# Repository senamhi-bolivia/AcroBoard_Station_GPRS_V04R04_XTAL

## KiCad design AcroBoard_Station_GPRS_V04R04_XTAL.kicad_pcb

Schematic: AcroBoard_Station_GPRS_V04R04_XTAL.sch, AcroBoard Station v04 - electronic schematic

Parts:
C1, C2, C4, C7, C10, C11, C12, C14, C22, C25, C34, C77, C78, C79, C80, C81, C82: 100nF; C_0603
C3, C16, C17: 1uF; C_0805
C5, C6, C8, C9, C20, C23, C24, C28, C35, C36, C39, C43, C44, C47, C48, C59, C62: 100nF; C_0402_NoSilk
C13: 68uF; CP_Tantalum_Case-D_EIA-7343-31_Reflow
C15, C19, C21: 22pF; C_0402_NoSilk
C18: 68uF; CP_Elec_5x5.8
C26: 470uF; CP_Radial_D10.0mm_P5.00mm
C27: 22uF; C_0805
C29, C30: 1nF; C_0402
C31, C37, C49, C51: 7pF; C_0402_NoSilk
C32, C38, C40: 33pF; C_0402_NoSilk
C33, C45, C46, C52, C53, C63: 4.7uF; C_0805
C41, C42: 22uF; C_1210
C50: 10uF; C_0805
C54, C55, C65, C66: 22uF; C_1206
C56: 330uF; CP_Elec_10x10
C57, C64, C69: 6.8nF; C_0603
C58, C72: 10uF; C_1210
C60, C61, C70, C71, C74, C75: 0.1uF; C_0805
C67: 4.7uF; CP_Elec_4x5.8
C68: 1uF; C_1206
C73: 100uF; CP_Elec_6.3x7.7
C76: 10uF; C_1206
Cv1, Cv2, Cv3: 0.1uF; C_0805
Cvs1, Cvs2, Cvs3: 1uF; C_0805
D1: Blue; LED_0603
D2, D3, D19: Green; LED_0603
D4, D9, D11, D14: SMBJ26CA; D_SMB
D5, D6, D12, D15: 1N4148W-V; D_SOD-123
D7: BZX84C10; SOT-23
D8, D18: STPS2L40U; D_SMB
D10, D13, D16: BAT54JFILM; D_SOD-323
D17: STPS3L40SY; D_SMC
D20: Red; LED_0603
FP1: {55.0,-148.0}; Fiducial_1mm_Dia_2.54mm_Outer_CopperTop
FP2: {55.0,-30.0}; Fiducial_1mm_Dia_2.54mm_Outer_CopperTop
FP3: {125.0,-148.0}; Fiducial_1mm_Dia_2.54mm_Outer_CopperTop
FP4: {125.0,-30.0}; Fiducial_1mm_Dia_2.54mm_Outer_CopperTop
FP5: {84.6,-79.9}; Fiducial_1mm_Dia_2.54mm_Outer_CopperTop
FP6: {90.0,-115.0}; Fiducial_1mm_Dia_2.54mm_Outer_CopperTop
FP7: {116.0,-89.0}; Fiducial_1mm_Dia_2.54mm_Outer_CopperTop
J1: Conn_Coaxial; SMA_THT_Jack_Straight
J2: Conn_01x08; Molex_KK-6410-08_08x2.54mm_Straight
J3: Conn_01x05; Molex_KK-6410-05_05x2.54mm_Straight
J4, J5: CONN_01X10; Molex_KK-6410-10_10x2.54mm_Straight
J6: CONN_01X08; Molex_KK-6410-08_08x2.54mm_Straight
J7: CONN_01X05; Molex_KK-6410-05_05x2.54mm_Straight
L1, L2, L3: FERRITE-BEAD-220ohm; L_0805
L4: INDUCTOR-3.1uH; SER80xx
L5: 10uH; 7447779122
LG1: ACRONET; ACRONET_logo_090
LG2: OSHW; OSHW-Logo_7.5x8mm_SilkScreen
MH1, MH2, MH3, MH4: MH; MountingHole_320_500-NPTH
P1: CONN_02X06; Socket_Strip_Straight_2x06_Pitch2.54mm_SMD
P2: CONN_14X2; Socket_Strip_Straight_2x14_Pitch2.00mm
P3: 10k B=3.380; Measurement_Point_Round-TH_Small
P4: CONN_5X2; Socket_Strip_Straight_2x05_Pitch2.00mm
P5: CONN_5; BM05B-SRSS-TB
P6: CONN_3; Molex_KK-6410-03_03x2.54mm_Straight
Q4: Si2319CDS; SOT-23
Q5, Q9, Q10: BSS138; SOT-23
Q6, Q7, Q8: IRF9362; SOIC-8_3.9x4.9mm_Pitch1.27mm
R1, R2, R65, R66: 4k7; R_0603
R3, R4, R5, R56, R62, R63, R64, R67: 330R; R_0603
R6, R7, R8: 51R; R_0402
R9, R22, R45, R55, R68: 100K; R_0603
R10: 90k; R_0603
R11, R18, R19, R29, R54: 10K; R_0603
R12: 24K; R_0603
R13, R17, R71, R72, R73, R75, R76, R78: 1K; R_0603
R14: 180K; R_0603
R15: 698K; R_0603
R16, R51: 174K; R_0603
R20, R36, R39, R40, R46, R47: 1M; R_0603
R21, R44: 215K; R_0603
R23, R30: 1M02; R_0805
R24, R69: 48K7; R_0805
R25, R32: 76K8; R_0805
R26: 698K; R_0805
R27: 27K; R_0805
R28: 49K9; R_0805
R31: 36K5; R_0805
R33: 0R; R_0805
R34, R35, R49, R50, R53, R79, R80, R81, R82: 309K; R_0603
R37: 73.2K; R_0603
R38, R41, R48: 2k21; R_0603
R42, R43: 1k3; R_0805
R52: 4K7; R_0603
R57: 0R05; R_1206
R58, R61: 5K1; R_0603
R59, R60: 2k0; R_0805
R70, R74, R77: 5K6; R_0603
SW1: DTSM-32S-B
T1, T2, T3, T4, T5, T6, T7, T8, T9, T10: PDTC143XU; SOT-323_SC-70
U1, U2, U3: AT24CM01-SSHD-B; SOIC-8_3.9x4.9mm_Pitch1.27mm
U4: MB85RC1MTPNF-G-JNERE1; SOIC-8_3.9x4.9mm_Pitch1.27mm
U5, U6: SP336EEY-L; TSSOP-28_4.4x9.7mm_Pitch0.65mm
U7: 78723-1001
U8: ESDA6V1-5W6; SOT363_ESDA6V1-5W6
U9: NCP3170; SOIC-8_3.9x4.9mm_Pitch1.27mm
U10: TPS737; SOT-223-6
U11: ATXMEGA256A3U; TQFP-64_14x14mm_Pitch0.8mm
U13: SIM800C; SIMCom_SIM800C
U14: LTC4417IGN; SSOP-24_3.9x8.7mm_Pitch0.635mm
U15, U16, U21, U22: FPF2701MX; SOP-8_FPF2701MX
U17: LT3652EMSE; MSOP12_LT3652EMSE_HandSoldering
U18, U19: ACPL-M21L; SO-5_ACPL-M21L
U20: MIC1555; SOT-23-5
U23: PCA9517ADP; TSSOP-8_3x3mm_Pitch0.65mm
U24: MPL3115A2; LGA-8_3x5mm_Pitch1.25mm
U25: PCAL9554B; TSSOP-16_4.4x5mm_Pitch0.65mm
U26: PCAL9535APW; TSSOP-24_4.4x7.8mm_Pitch0.65mm
Y1: Crystal; Crystal_SMD_MicroCrystal_CC7V-T1A-2pin_3.2x1.5mm

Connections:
/ALT_CHARGE: J3.2, Q10.3 (D), R58.2
/BC_NC_FET: D7.1 (A), Q4.1 (G), R19.1, R22.2
/BC_NTC: P3.1, U17.8 (NTC)
/BC_Timer: C53.2, U17.6 (TIMER)
/BC_Vin: C56.1, C58.1, C59.1, D7.3 (K), D8.1 (K), D19.2 (A), D20.2 (A), J3.5, Q4.2 (S), R22.1, R36.2, R40.2, U17.1 (Vin)
/CLED_CMD: Q5.3 (D), Q10.1 (G), R37.1
/CMD_PSW1: R79.1, U16.4 (ON), U26.16 (P1_3)
/CMD_PSW2: R80.1, U15.4 (ON), U26.15 (P1_2)
/CMD_PSW3: R82.1, U22.4 (ON), U26.14 (P1_1)
/CMD_PSW4: R81.1, U21.4 (ON), U26.13 (P1_0)
/I2C_OUT_SCL: P4.3, U23.2 (SCLA)
/I2C_OUT_SDA: P4.1, U23.3 (SDAA)
/I2C_SIG: P4.7, T3.3 (C)
/I2C_VIN: C79.2, P4.5, U23.1 (VCCA)
/MCU_Status_LED: T1.1 (B), U11.26 (PD0)
/NETLIGHT: T9.1 (B), U13.41 (NETLIGHT)
/NValid1: U14.10 (~VALID1), U26.6 (P0_2)
/NValid2: U14.11 (~VALID2), U26.5 (P0_1)
/NValid3: U14.12 (~VALID3), U26.4 (P0_0)
/N_SHDN: R18.1, U14.2 (~SHDN)
/OC1: J7.2, R62.2
/OC2: J7.3, R63.2
/OC3: J7.4, R64.2
/OC4: J7.5, R67.2
/PA0: C34.1, P2.1, U11.62 (PA0)
/PA1: R10.2, R11.1, U11.63 (PA1)
/PA2: P2.3, U11.64 (PA2)
/PA3: P2.5, U11.1 (PA3)
/PA4: P2.7, U11.2 (PA4)
/PA5: P2.9, U11.3 (PA5)
/PA6: P2.11, U11.4 (PA6)
/PA7: P2.13, U11.5 (PA7)
/PB0: C35.1, P2.15, U11.6 (PB0)
/PB1: P2.17, U11.7 (PB1)
/PB2: P2.19, U11.8 (PB2)
/PB3: P2.21, U11.9 (PB3)
/PB4: P2.23, U11.10 (PB4)
/PB5: P2.25, U11.11 (PB5)
/PB6: P2.27, U11.12 (PB6)
/PB7: U11.13 (PB7), U23.5 (EN)
/PC0: R66.2, U11.16 (PC0), U23.6 (SDAB)
/PC1: R65.2, U11.17 (PC1), U23.7 (SCLB)
/PC2: U5.19 (R1_Out), U11.18 (PC2)
/PC3: U5.26 (TI_In), U11.19 (PC3)
/PC4: U5.27 (T2_In), U11.20 (PC4)
/PC5: U5.1 (T4_In), U11.21 (PC5)
/PC6: U5.21 (R3_Out), U11.22 (PC6)
/PC7: U5.28 (T3_In), U11.23 (PC7)
/PCAL_P3: T5.1 (B), U26.7 (P0_3)
/PCAL_P4: T6.1 (B), U26.8 (P0_4)
/PCAL_P5: T7.1 (B), U26.9 (P0_5)
/PCAL_P6: T8.1 (B), U26.10 (P0_6)
/PCAL_P7: T4.1 (B), U26.11 (P0_7)
/PD1: T3.1 (B), U11.27 (PD1)
/PD2: U6.19 (R1_Out), U11.28 (PD2)
/PD3: U6.26 (TI_In), U11.29 (PD3)
/PD4: U6.27 (T2_In), U11.30 (PD4)
/PD5: U6.1 (T4_In), U11.31 (PD5)
/PD6: U6.21 (R3_Out), U11.32 (PD6)
/PD7: U6.28 (T3_In), U11.33 (PD7)
/PDI_CLK: P1.4, R29.1, U11.57 (~RESET)
/PDI_DATA: P1.6, U11.56 (PDI)
/PE0: R1.2, U1.5 (SDA), U2.5 (SDA), U3.5 (SDA), U4.5 (SDA), U11.36 (PE0), U24.7 (SDL), U25.15 (SDA), U26.23 (SDA)
/PE1: R2.2, U1.6 (SCL), U2.6 (SCL), U3.6 (SCL), U4.6 (SCL), U11.37 (PE1), U24.8 (SCL), U25.14 (SCL), U26.22 (SCL)
/PF3: T2.1 (B), U11.49 (PF3)
/PF4: T10.1 (B), U11.50 (PF4)
/PF6: P1.10, U11.54 (PF6)
/PF7: P1.8, U11.55 (PF7)
/PG: R68.2, R69.1, U9.7 (PG), U10.5 (EN)
/PR0: U11.58 (PR0), U18.5 (VO)
/PR1: U11.59 (PR1), U19.5 (VO)
/PSW1: C61.1, J6.1, U16.8 (VOUT)
/PSW2: C60.1, J6.3, U15.8 (VOUT)
/PSW3: C75.1, J6.5, U22.8 (VOUT)
/PSW4: C74.1, J6.7, U21.8 (VOUT)
/PULSE1: P6.3, R43.1
/PULSE2: P6.1, R42.1
/PWRKEY: C24.1, T2.3 (C), U13.39 (~PWRKEY)
/Panel+: D4.1 (A1), D8.2 (A), J3.4, Q4.3 (D)
/RF_ANT: J1.1 (In), U13.32 (GSM_ANT)
/RING_TO_SIM: R71.1, U13.7 (UART1_RI)
/RX1: J4.2, U5.15 (R1_In)
/RX2: J4.3, U5.16 (R2_In)
/RX2_1: J5.2, U6.15 (R1_In)
/RX2_2: J5.3, U6.16 (R2_In)
/RX2_3: J5.7, U6.17 (R3_In)
/RX2_4: J5.8, U6.18 (R4_In)
/RX3: J4.7, U5.17 (R3_In)
/RX4: J4.8, U5.18 (R4_In)
/S900CTS: R72.2, U11.41 (PE5)
/S900RI: R71.2, U11.46 (PF0)
/S900STATUS: R78.1, U11.47 (PF1)
/SIMCTS_TO_SIM: R72.1, U13.4 (UART1_CTS)
/SIM_CLK: C19.1, R7.2, U13.16 (SIM_CLK)
/SIM_CLK_0: R7.1, U7.3 (CLK), U8.1 (I/O1)
/SIM_DATA: C15.1, R6.2, U13.15 (SIM_DATA)
/SIM_DATA_0: R6.1, U7.7 (I/O), U8.6 (I/O4)
/SIM_RST: C21.1, R8.1, U13.17 (SIM_RST)
/SIM_RST_0: R8.2, U7.2 (RST), U8.3 (I/O2)
/SIM_RXD: R76.1, R77.2, U13.2 (UART1_RXD)
/SIM_TXD: R75.1, U13.1 (UART1_TXD)
/SIM_USB_DM: P5.4, U13.26 (USB_DM)
/SIM_USB_DP: P5.3, U13.25 (USB_DP)
/SIM_USB_VBUS: P5.1, U13.24 (USB_VBUS)
/SIM_VDD: C23.1, U7.1 (Vcc), U8.4 (I/O3), U13.18 (SIM_VDD)
/SIM_VDDEXT: U13.40 (VDD_EXT)
/SP336_2_M0: U6.24 (MODE_0), U25.6 (P2)
/SP336_2_M1: U6.2 (MODE_1), U25.4 (P0)
/SP336_2_M2: U6.23 (MODE_2), U25.5 (P1)
/SP336_2_SLEW: U6.25 (SLEW), U25.7 (P3)
/SP336_M0: U5.24 (MODE_0), U25.10 (P5)
/SP336_M1: U5.2 (MODE_1), U25.12 (P7)
/SP336_M2: U5.23 (MODE_2), U25.11 (P6)
/SP336_SLEW: U5.25 (SLEW), U25.9 (P4)
/STATUS_PSW1: U16.7 (FLAGB), U26.20 (P1_7)
/STATUS_PSW2: U15.7 (FLAGB), U26.19 (P1_6)
/STATUS_PSW3: U22.7 (FLAGB), U26.18 (P1_5)
/STATUS_PSW4: U21.7 (FLAGB), U26.17 (P1_4)
/THR: C67.1, R47.2, U20.5 (THR)
/TOSC1: C49.1, U11.43 (TOSC1), Y1.1
/TOSC2: C51.1, U11.42 (TOSC2), Y1.2
/TRG: R45.2, T4.3 (C), U20.4 (TRG)
/TX1: J4.4, U5.6 (T1_Out)
/TX2: J4.5, U5.7 (T2_Out)
/TX2_1: J5.4, U6.6 (T1_Out)
/TX2_2: J5.5, U6.7 (T2_Out)
/TX2_3: J5.9, U6.4 (T3_Out)
/TX2_4: J5.10, U6.3 (T4_Out)
/TX3: J4.9, U5.4 (T3_Out)
/TX4: J4.10, U5.3 (T4_Out)
/VBAT: P1.12, U11.51 (VBAT)
/VPULSE1: R59.1, U19.1 (A)
/VPULSE2: R60.1, U18.1 (A)
/VPrimary: C72.1, C73.1, Cv2.1, D11.1 (A1), D18.2 (A), J2.2, Q7.7 (D1), Q7.8 (D1), R26.1, R39.2, R53.2, R57.1, U14.23 (V2), U17.9 (BAT)
/VRTC_SIM: C46.2, U13.28 (VRTC)
/Vbackup: Cv1.1, D14.1 (A1), J2.4, Q8.7 (D1), Q8.8 (D1), R30.1, U14.22 (V3)
/Vcc-3: C3.1, L1.2, U5.5 (VCC)
/Vcc-5: C16.1, L2.2, U6.5 (VCC)
/Vin_reg: D6.2 (A), R40.1, R44.1, U17.2 (Vin_reg)
/Vwall: Cv3.1, D9.1 (A1), J2.6, Q6.7 (D1), Q6.8 (D1), R23.1, U14.24 (V1)
/XMDTR: R13.2, U11.48 (PF2)
/XMDTR_TO_SIM: R13.1, R70.2, U13.6 (UART1_DTR)
/XMRTS: R73.2, U11.40 (PE4)
/XMRTS_TO_SIM: R73.1, R74.2, U13.3 (UART1_RTS)
/XMRXD-S900TXD: R75.2, U11.38 (PE2)
/XMTXD-S900RXD: R76.2, U11.39 (PE3)
/~BC_SHDN: R36.1, R37.2, U17.3 (~SHDN)
/~CHARGE: D5.2 (A), D12.2 (A), Q5.1 (G), R19.2, R39.1, U17.4 (~CHRG)
/~FAULT: J3.1, R61.2, U17.5 (~FAULT)
GND: C3.2, C4.1, C5.2, C6.2, C7.1, C8.2, C9.2, C10.2, C13.2, C14.2, C15.2, C16.2, C17.2, C18.2, C19.2, C20.2, C21.2, C22.1, C23.2, C24.2, C25.1, C26.2, C27.2, C28.2, C29.2, C30.1, C33.2, C34.2, C35.2, C36.2, C37.2, C38.2, C39.2, C41.2, C42.2, C43.2, C44.2, C45.1, C46.1, C47.2, C48.2, C49.2, C50.2, C51.2, C52.1, C53.1, C54.2, C55.2, C56.2, C58.2, C59.2, C60.2, C61.2, C62.2, C63.1, C65.2, C66.2, C67.2, C70.2, C71.2, C72.2, C73.2, C74.2, C75.2, C76.2, C77.2, C78.2, C79.1, C80.1, C81.1, C82.1, Cv1.2, Cv2.2, Cv3.2, Cvs1.2, Cvs2.2, Cvs3.2, D2.1 (K), D4.2 (A2), D9.2 (A2), D11.2 (A2), D14.2 (A2), D17.2 (A), J1.2 (Ext), J2.1, J2.3, J2.5, J2.7, J3.3, J4.1, J4.6, J5.1, J5.6, J6.2, J6.4, J6.6, J6.8, P1.1, P1.3, P1.5, P1.7, P1.9, P1.11, P2.2, P2.4, P2.6, P2.8, P2.10, P2.12, P2.14, P2.16, P2.18, P2.20, P2.22, P2.24, P2.26, P2.28, P4.2, P4.4, P4.6, P5.5, Q5.2 (S), Q9.2 (S), Q10.2 (S), R12.1, R16.2, R21.2, R25.2, R28.2, R32.2, R33.2, R34.1, R35.1, R44.2, R46.2, R49.1, R50.1, R54.2, R55.2, R69.2, R70.1, R74.1, R77.1, T1.2 (E), T2.2 (E), T3.2 (E), T4.2 (E), T5.2 (E), T6.2 (E), T7.2 (E), T8.2 (E), T9.2 (E), T10.2 (E), U1.4 (GND), U1.7 (WP), U2.2 (A1), U2.4 (GND), U2.7 (WP), U3.3 (A2), U3.4 (GND), U3.7 (WP), U4.2 (A1), U4.3 (A2), U4.4 (GND), U4.7 (WP), U5.8 (GND), U6.8 (GND), U7.5 (GND), U7.11 (GND1), U7.12 (GND2), U7.13 (GND3), U7.14 (GND4), U7.15 (GND5), U7.16 (GND6), U8.2 (GND), U9.1 (PGND), U9.3 (AGND), U10.3 (GND), U10.6 (GND), U11.14 (GND), U11.24 (GND), U11.34 (GND), U11.44 (GND), U11.52 (GND), U11.60 (GND), U13.8 (GND), U13.13 (GND), U13.19 (GND), U13.21 (GND), U13.27 (GND), U13.30 (GND), U13.31 (GND), U13.33 (GND), U13.36 (GND), U13.37 (GND), U14.13 (GND), U15.2 (PGOOD), U15.5 (GND), U16.2 (PGOOD), U16.5 (GND), U17.13 (GND), U18.4 (GND), U19.4 (GND), U20.2 (GND), U21.2 (PGOOD), U21.5 (GND), U22.2 (PGOOD), U22.5 (GND), U23.4 (GND), U24.3 (GND), U25.1 (A0), U25.2 (A1), U25.3 (A2), U25.8 (GND), U26.3 (A2), U26.12 (VSS), U26.21 (A0)
unnamed: C1.1, U5.12 (C1-)
unnamed: C1.2, U5.9 (C1+)
unnamed: C2.1, U5.13 (C2-)
unnamed: C2.2, U5.11 (C2+)
unnamed: C4.2, U5.14 (V-)
unnamed: C7.2, U5.10 (V+)
unnamed: C10.1, R3.1, R4.1, R5.2, SW1.2 (B)
unnamed: C11.1, U6.12 (C1-)
unnamed: C11.2, U6.9 (C1+)
unnamed: C12.1, U6.13 (C2-)
unnamed: C12.2, U6.11 (C2+)
unnamed: C22.2, U6.14 (V-)
unnamed: C25.2, U6.10 (V+)
unnamed: C31.1, C32.1, U9.5 (COMP)
unnamed: C31.2, C40.1, R14.2, R15.2, R16.1, U9.4 (FB1)
unnamed: C32.2, R14.1
unnamed: C39.1, L3.2, U11.61 (AVCC)
unnamed: C40.2, R17.1
unnamed: C52.2, D5.1 (K), D6.1 (K), R20.2
unnamed: C57.2, D10.1 (K), Q6.2 (G1), Q6.4 (G2), R38.1
unnamed: C63.2, D12.1 (K), D15.1 (K), R46.1
unnamed: C64.2, D13.1 (K), Q7.2 (G1), Q7.4 (G2), R41.1
unnamed: C68.1, D17.1 (K), L5.2, U17.12 (SW)
unnamed: C68.2, D18.1 (K), U17.11 (BOOST)
unnamed: C69.2, D16.1 (K), Q8.2 (G1), Q8.4 (G2), R48.1
unnamed: C78.1, U24.2 (CAP)
unnamed: Cvs1.1, Q6.1 (S1), Q6.3 (S2), U14.21 (VS1)
unnamed: Cvs2.1, Q7.1 (S1), Q7.3 (S2), U14.19 (VS2)
unnamed: Cvs3.1, Q8.1 (S1), Q8.3 (S2), U14.17 (VS3)
unnamed: D1.1 (K), T9.3 (C)
unnamed: D1.2 (A), R3.2
unnamed: D2.2 (A), R4.2
unnamed: D3.1 (K), T1.3 (C)
unnamed: D3.2 (A), R5.1
unnamed: D10.2 (A), R38.2, U14.20 (G1)
unnamed: D13.2 (A), R41.2, U14.18 (G2)
unnamed: D15.2 (A), R51.1, R53.1, R55.1
unnamed: D16.2 (A), R48.2, U14.16 (G3)
unnamed: D19.1 (K), R58.1
unnamed: D20.1 (K), R61.1
unnamed: J2.8, R18.2
unnamed: L4.1, U9.8 (VSW)
unnamed: L5.1, R57.2, U17.10 (SENSE)
unnamed: P6.2, R59.2, R60.2
unnamed: Q9.1 (G), R52.2, R54.1
unnamed: Q9.3 (D), R56.2
unnamed: R11.2, T10.3 (C)
unnamed: R20.1, R21.1
unnamed: R23.2, R24.1, U14.4 (UV1)
unnamed: R24.2, R25.1, U14.5 (OV1)
unnamed: R26.2, R27.1, U14.6 (UV2)
unnamed: R27.2, R28.1, U14.7 (OV2)
unnamed: R30.2, R31.1, U14.8 (UV3)
unnamed: R31.2, R32.1, U14.9 (OV3)
unnamed: R33.1, U14.3 (HYS)
unnamed: R34.2, U16.3 (ISET)
unnamed: R35.2, U15.3 (ISET)
unnamed: R42.2, U18.3 (C)
unnamed: R43.2, U19.3 (C)
unnamed: R47.1, R52.1, U20.3 (OUT)
unnamed: R49.2, U21.3 (ISET)
unnamed: R50.2, U22.3 (ISET)
unnamed: R51.2, U17.7 (Vfb)
unnamed: R62.1, T5.3 (C)
unnamed: R63.1, T6.3 (C)
unnamed: R64.1, T7.3 (C)
unnamed: R67.1, T8.3 (C)
unnamed: R78.2, U13.42 (STATUS)
SW3: C29.1, R9.2, R12.2, R56.1, U9.6 (EN)
V3.3: C5.1, C6.1, C8.1, C9.1, C33.1, C36.1, C43.1, C44.1, C45.2, C47.1, C48.1, C70.1, C71.1, C76.1, C77.1, C80.2, C81.2, C82.2, L1.1, L2.1, L3.1, P1.2, P4.9, R1.1, R2.1, R29.2, R65.1, R66.1, R79.2, R80.2, R81.2, R82.2, U1.2 (A1), U1.3 (A2), U1.8 (VCC), U2.3 (A2), U2.8 (VCC), U3.2 (A1), U3.8 (VCC), U4.8 (VCC), U10.2 (OUT), U11.15 (VDD), U11.25 (VDD), U11.35 (VCC), U11.45 (VCC), U11.53 (VCC), U18.6 (VDD), U19.6 (VDD), U23.8 (VCCB), U24.1 (Vdd), U24.4 (VDDIO), U25.16 (VDD), U26.2 (A1), U26.24 (VDD)
V4.0: C13.1, C14.1, C17.1, C18.1, C20.1, C37.1, C38.1, C41.1, C42.1, C50.1, L4.2, R15.1, R17.2, SW1.1 (A), U10.1 (IN), U13.34 (VBAT), U13.35 (VBAT)
VSelected: C26.1, C27.1, C28.1, C30.2, C54.1, C55.1, C57.1, C62.1, C64.1, C65.1, C66.1, C69.1, J7.1, P4.8, P4.10, Q6.5 (D2), Q6.6 (D2), Q7.5 (D2), Q7.6 (D2), Q8.5 (D2), Q8.6 (D2), R9.1, R10.1, R45.1, R68.1, U9.2 (VIN), U14.15 (VOUT), U15.1 (VIN), U16.1 (VIN), U20.1 (VS), U21.1 (VIN), U22.1 (VIN)

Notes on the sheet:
GND
RS485/RS232 Transceiver
Mounting Holes
Board Connector 5
3V3
GPRS Debug Connector
USB_DM
USB_DP
P2out
Board Connector 4
PF7
PF6
2V8
VBAT
PA5
PA6
PA7
PB0
PB1
PB2
PB3
PB4
PB5
Board Connector 3
GPRS Switch
Pulse Signal Stage
VPin
P1out
Board Connector 1
Pulse Signal Connector
Battery Voltmeter
Status LED Module
XMEGA MCU
I2C EEPROM Memory Module
MCU Status LED
Power ON LED
AcroBoard Station v03 r02 Released under the Creative Commons Attribution Share-Alike 4.0 Unported license (http://creativecommons.org/licenses/by-sa/4.0/) and the Open Source Hardware (OSHW) Definition 1.0 (http://freedomdefined.org/OSHW) Designed by ACRONET® 2016 (http://www.acronet.cc)
Logos
PA4
THIS ELECTRONIC SCHEMATIC IS PROVIDED "AS IS" AND "WITH ALL FAULTS". ACRONET® DISCLAIMS ALL OTHER WARRANTIES, EXPRESS OR IMPLIED, REGARDING PRODUCTS, INCLUDING BUT NOT LIMITED TO, ANY IMPLIED WARRANTIES OF MERCHANTABILITY OR FITNESS FOR A PARTICULAR PURPOSE.

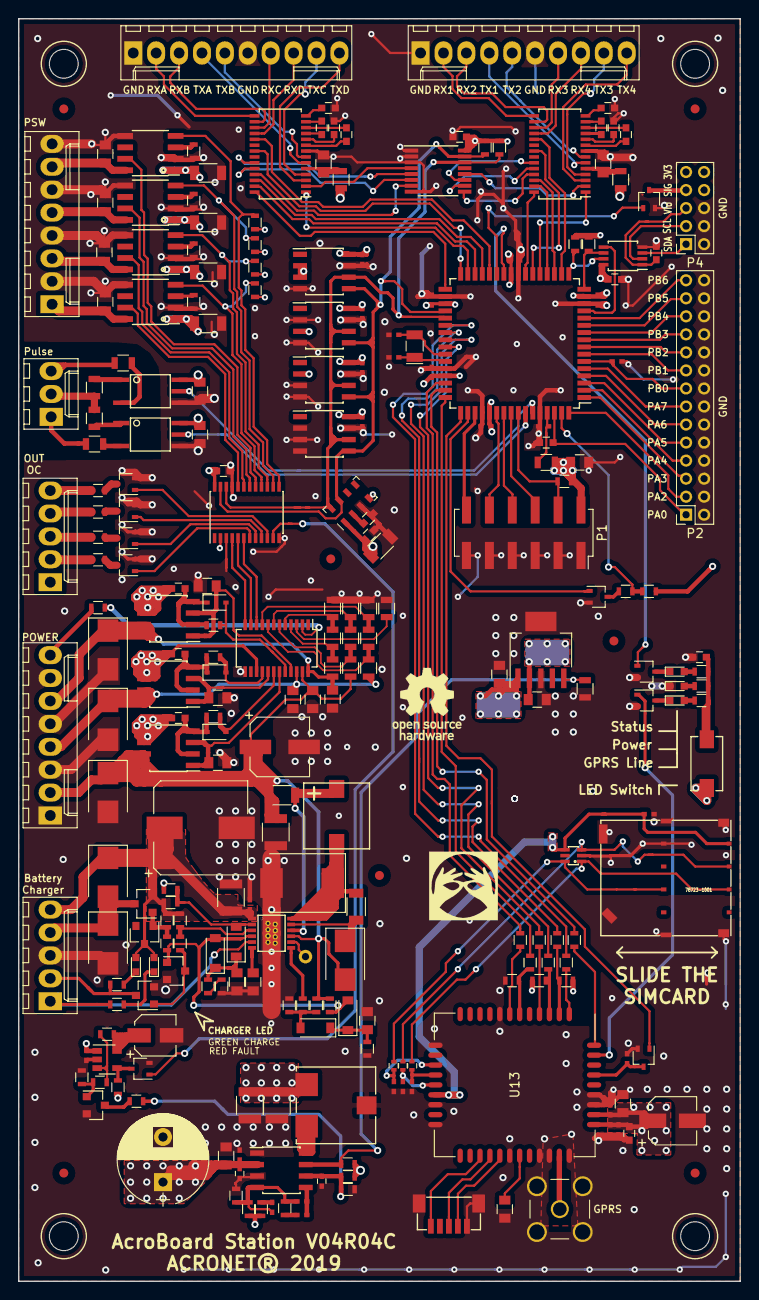
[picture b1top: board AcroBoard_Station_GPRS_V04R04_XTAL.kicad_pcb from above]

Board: 4 copper layers, 80.0 x 140.0 mm, 264 parts (0 on the bottom side), 221 nets.

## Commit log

2019-05-08 imported from Cima
